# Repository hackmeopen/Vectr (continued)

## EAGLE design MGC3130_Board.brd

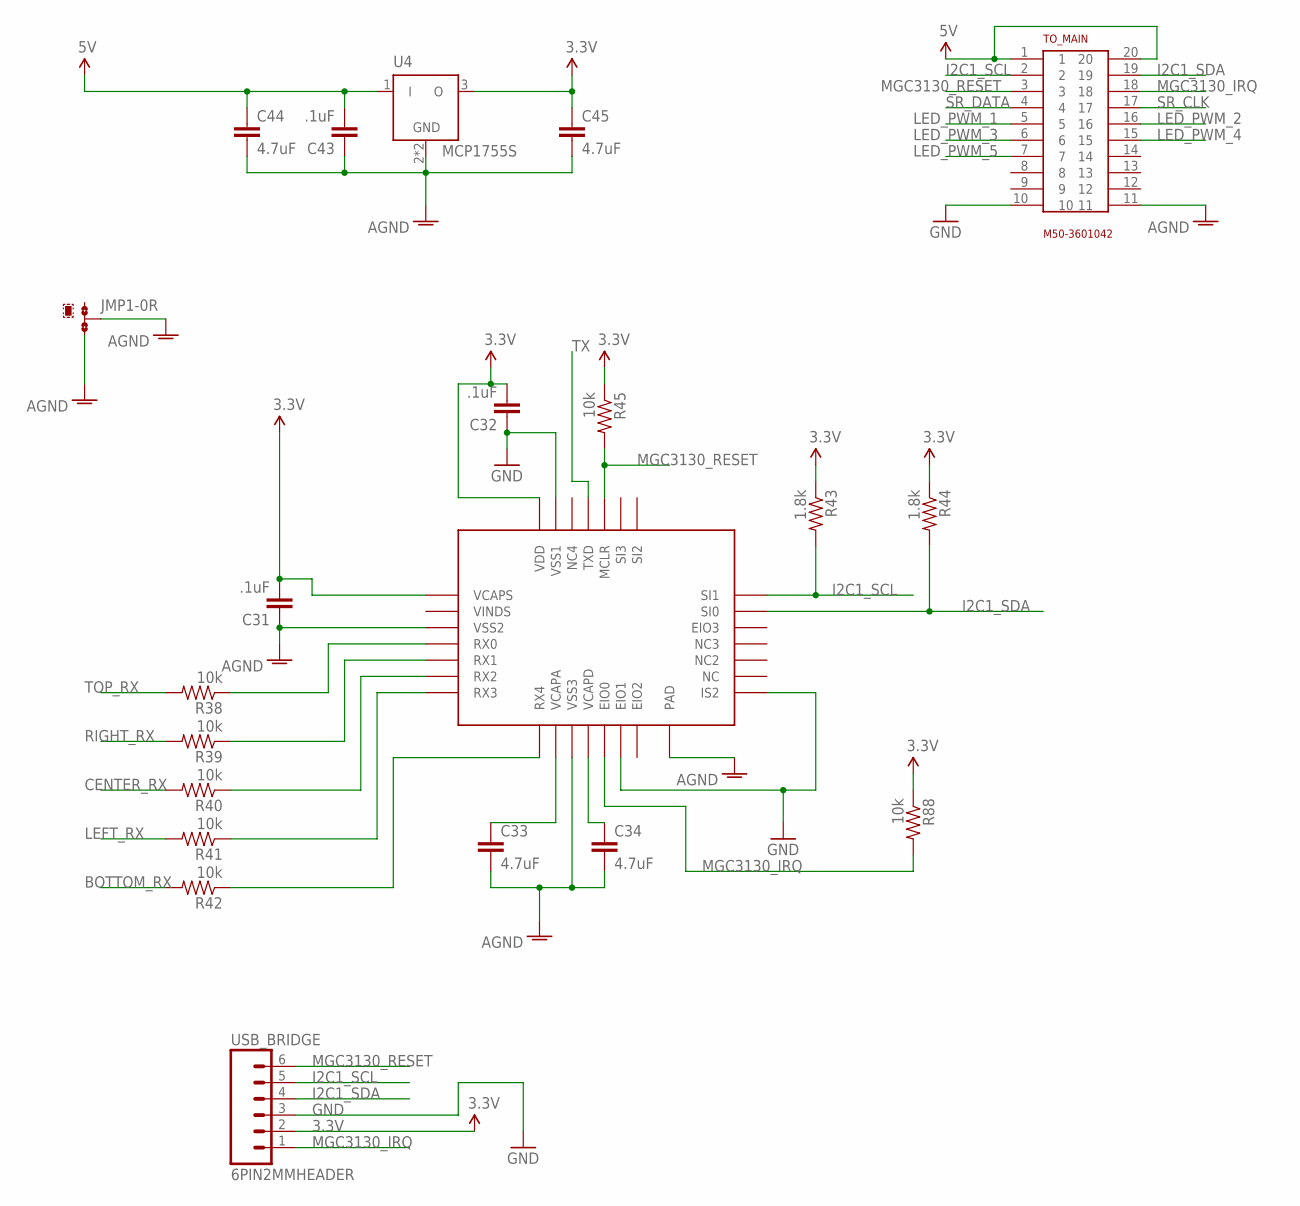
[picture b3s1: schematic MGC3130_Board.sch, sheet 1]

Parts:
C31, C32, C43: .1uF; 0603-CAP
C33, C34, C44, C45: 4.7uF; 1206
JMP1: 0R-JUMPA; A0R-JMP
R38, R39, R40, R41, R42, R45, R88: 10k; 0603-RES
R43, R44: 1.8k; 0603-RES
TO_MAIN: M50-3601042
U4: MCP1755S; SOT223
U14: MGC3130; QFN28
USB_BRIDGE: 6PIN2MMHEADER; 1X06_SMD_STRAIGHT

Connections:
3.3V: C31.2, C32.2, C45.1, R43.1, R44.1, R45.1, R88.1, U4.3 (O), U14.P$1 (VCAPS), U14.P$28 (VDD), USB_BRIDGE.2
5V: C43.2, C44.1, TO_MAIN.1, TO_MAIN.20, U4.1 (I); also elsewhere on the board
AGND: C31.1, C33.2, C34.2, C43.1, C44.2, C45.2, JMP1.2, JMP1.3, TO_MAIN.11, U4.2 (GND), U4.4 (GND), U14.P$3 (VSS2), U14.P$10 (VSS3), U14.P$29 (PAD)
BOTTOM_RX: R42.2
CENTER_RX: R40.2
GND: C32.1, TO_MAIN.10, U14.P$13 (EIO1), U14.P$15 (IS2), U14.P$27 (VSS1), USB_BRIDGE.3; also elsewhere on the board
I2C1_SCL: R43.2, TO_MAIN.2, U14.P$21 (SI1), USB_BRIDGE.5
I2C1_SDA: R44.2, TO_MAIN.19, U14.P$20 (SI0), USB_BRIDGE.4
LED_PWM_1: TO_MAIN.5; also elsewhere on the board
LED_PWM_2: TO_MAIN.16; also elsewhere on the board
LED_PWM_3: TO_MAIN.6; also elsewhere on the board
LED_PWM_4: TO_MAIN.15; also elsewhere on the board
LED_PWM_5: TO_MAIN.7; also elsewhere on the board
LEFT_RX: R41.2
MGC3130_IRQ: R88.2, TO_MAIN.18, U14.P$12 (EIO0), USB_BRIDGE.1
MGC3130_RESET: R45.2, TO_MAIN.3, U14.P$24 (MCLR), USB_BRIDGE.6
unnamed: R38.1, U14.P$4 (RX0)
unnamed: R39.1, U14.P$5 (RX1)
unnamed: R40.1, U14.P$6 (RX2)
unnamed: R41.1, U14.P$7 (RX3)
unnamed: R42.1, U14.P$8 (RX4)
unnamed: C33.1, U14.P$9 (VCAPA)
unnamed: C34.1, U14.P$11 (VCAPD)
RIGHT_RX: R39.2
SR_CLK: TO_MAIN.17; also elsewhere on the board
SR_DATA: TO_MAIN.4; also elsewhere on the board
TOP_RX: R38.2
TX: U14.P$25 (TXD)

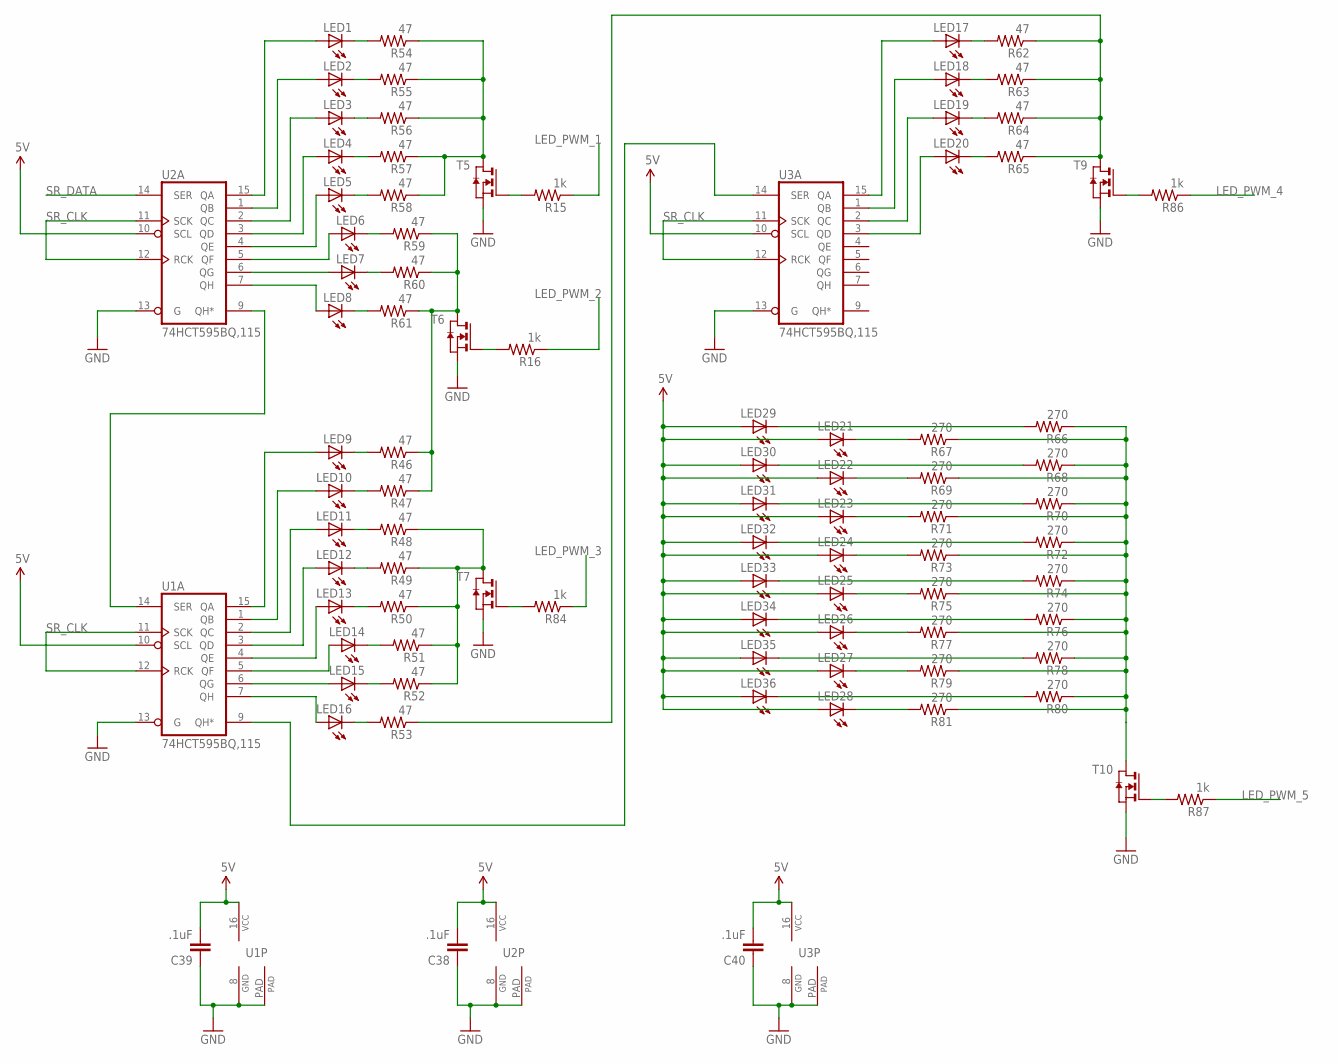
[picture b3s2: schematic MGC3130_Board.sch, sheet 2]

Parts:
C38, C39, C40: .1uF; 0603-CAP
LED1, LED2, LED3, LED4, LED5, LED6, LED7, LED8, LED9, LED10, LED11, LED12, LED13, LED14, LED15, LED16, LED17, LED18, LED19, LED20: APA3010QBC/D-GX; APA3010
LED21, LED22, LED23, LED24, LED25, LED26, LED27, LED28, LED29, LED30, LED31, LED32, LED33, LED34, LED35, LED36: APA3010SRCPRV-GX; APA3010
R15, R16, R84, R86, R87: 1k; 0603-RES
R46, R47, R48, R49, R50, R51, R52, R53, R54, R55, R56, R57, R58, R59, R60, R61, R62, R63, R64, R65: 47; 0603-RES
R66, R67, R68, R69, R70, R71, R72, R73, R74, R75, R76, R77, R78, R79, R80, R81: 270; 0603-RES
T5, T6, T7, T9, T10: NMOSSOT23; SOT-23
U1, U2, U3: 74HCT595BQ,115; DHVQFN16

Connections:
5V: C38.2, C39.2, C40.2, LED21.P$2 (A), LED22.P$2 (A), LED23.P$2 (A), LED24.P$2 (A), LED25.P$2 (A), LED26.P$2 (A), LED27.P$2 (A), LED28.P$2 (A), LED29.P$2 (A), LED30.P$2 (A), LED31.P$2 (A), LED32.P$2 (A), LED33.P$2 (A), LED34.P$2 (A), LED35.P$2 (A), LED36.P$2 (A), U1.10 (SCL), U1.16 (VCC), U2.10 (SCL), U2.16 (VCC), U3.10 (SCL), U3.16 (VCC); also elsewhere on the board
GND: C38.1, C39.1, C40.1, T5.2 (S), T6.2 (S), T7.2 (S), T9.2 (S), T10.2 (S), U1.8 (GND), U1.13 (G), U1.PAD (GND1), U2.8 (GND), U2.13 (G), U2.PAD (GND1), U3.8 (GND), U3.13 (G), U3.PAD (GND1); also elsewhere on the board
LED_PWM_1: R15.1; also elsewhere on the board
LED_PWM_2: R16.1; also elsewhere on the board
LED_PWM_3: R84.1; also elsewhere on the board
LED_PWM_4: R86.1; also elsewhere on the board
LED_PWM_5: R87.1; also elsewhere on the board
unnamed: LED29.P$1 (C), R66.2
unnamed: LED21.P$1 (C), R67.2
unnamed: LED30.P$1 (C), R68.2
unnamed: LED22.P$1 (C), R69.2
unnamed: LED31.P$1 (C), R70.2
unnamed: LED15.P$2 (A), U1.6 (QG)
unnamed: LED23.P$1 (C), R71.2
unnamed: LED32.P$1 (C), R72.2
unnamed: LED24.P$1 (C), R73.2
unnamed: LED34.P$1 (C), R76.2
unnamed: LED33.P$1 (C), R74.2
unnamed: LED25.P$1 (C), R75.2
unnamed: LED26.P$1 (C), R77.2
unnamed: LED35.P$1 (C), R78.2
unnamed: LED27.P$1 (C), R79.2
unnamed: R15.2, T5.3 (G)
unnamed: LED36.P$1 (C), R80.2
unnamed: LED28.P$1 (C), R81.2
unnamed: LED1.P$2 (A), U2.15 (QA)
unnamed: LED2.P$2 (A), U2.1 (QB)
unnamed: LED3.P$2 (A), U2.2 (QC)
unnamed: LED4.P$2 (A), U2.3 (QD)
unnamed: LED5.P$2 (A), U2.4 (QE)
unnamed: LED6.P$2 (A), U2.5 (QF)
unnamed: LED7.P$2 (A), U2.6 (QG)
unnamed: LED8.P$2 (A), U2.7 (QH)
unnamed: LED1.P$1 (C), R54.2
unnamed: LED2.P$1 (C), R55.2
unnamed: LED3.P$1 (C), R56.2
unnamed: LED4.P$1 (C), R57.2
unnamed: LED5.P$1 (C), R58.2
unnamed: LED6.P$1 (C), R59.2
unnamed: LED7.P$1 (C), R60.2
unnamed: LED8.P$1 (C), R61.2
unnamed: R54.1, R55.1, R56.1, R57.1, R58.1, T5.1 (D)
unnamed: R46.1, R47.1, R59.1, R60.1, R61.1, T6.1 (D)
unnamed: LED9.P$2 (A), U1.15 (QA)
unnamed: LED10.P$2 (A), U1.1 (QB)
unnamed: LED11.P$2 (A), U1.2 (QC)
unnamed: LED12.P$2 (A), U1.3 (QD)
unnamed: LED13.P$2 (A), U1.4 (QE)
unnamed: LED14.P$2 (A), U1.5 (QF)
unnamed: LED16.P$2 (A), U1.7 (QH)
unnamed: LED9.P$1 (C), R46.2
unnamed: LED10.P$1 (C), R47.2
unnamed: LED11.P$1 (C), R48.2
unnamed: LED12.P$1 (C), R49.2
unnamed: LED13.P$1 (C), R50.2
unnamed: LED14.P$1 (C), R51.2
unnamed: LED15.P$1 (C), R52.2
unnamed: LED16.P$1 (C), R53.2
unnamed: R48.1, R49.1, R50.1, R51.1, R52.1, T7.1 (D)
unnamed: LED17.P$2 (A), U3.15 (QA)
unnamed: LED18.P$2 (A), U3.1 (QB)
unnamed: LED19.P$2 (A), U3.2 (QC)
unnamed: LED20.P$2 (A), U3.3 (QD)
unnamed: R66.1, R67.1, R68.1, R69.1, R70.1, R71.1, R72.1, R73.1, R74.1, R75.1, R76.1, R77.1, R78.1, R79.1, R80.1, R81.1, T10.1 (D)
unnamed: U1.14 (SER), U2.9 (QH*)
unnamed: LED17.P$1 (C), R62.2
unnamed: LED18.P$1 (C), R63.2
unnamed: LED19.P$1 (C), R64.2
unnamed: LED20.P$1 (C), R65.2
unnamed: R53.1, R62.1, R63.1, R64.1, R65.1, T9.1 (D)
unnamed: U1.9 (QH*), U3.14 (SER)
unnamed: R16.2, T6.3 (G)
unnamed: R84.2, T7.3 (G)
unnamed: R86.2, T9.3 (G)
unnamed: R87.2, T10.3 (G)
SR_CLK: U1.11 (SCK), U1.12 (RCK), U2.11 (SCK), U2.12 (RCK), U3.11 (SCK), U3.12 (RCK); also elsewhere on the board
SR_DATA: U2.14 (SER); also elsewhere on the board

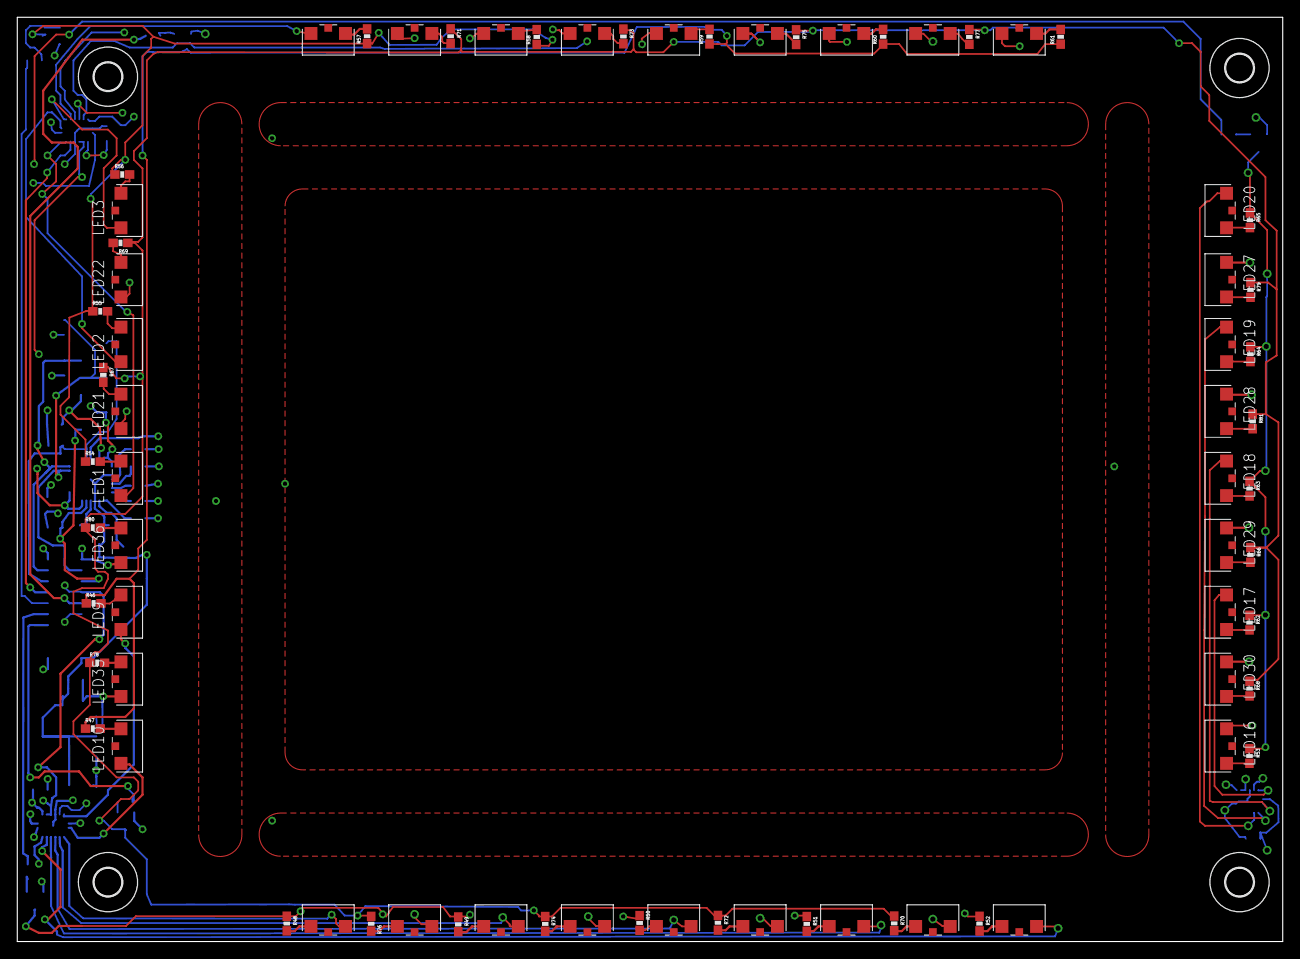
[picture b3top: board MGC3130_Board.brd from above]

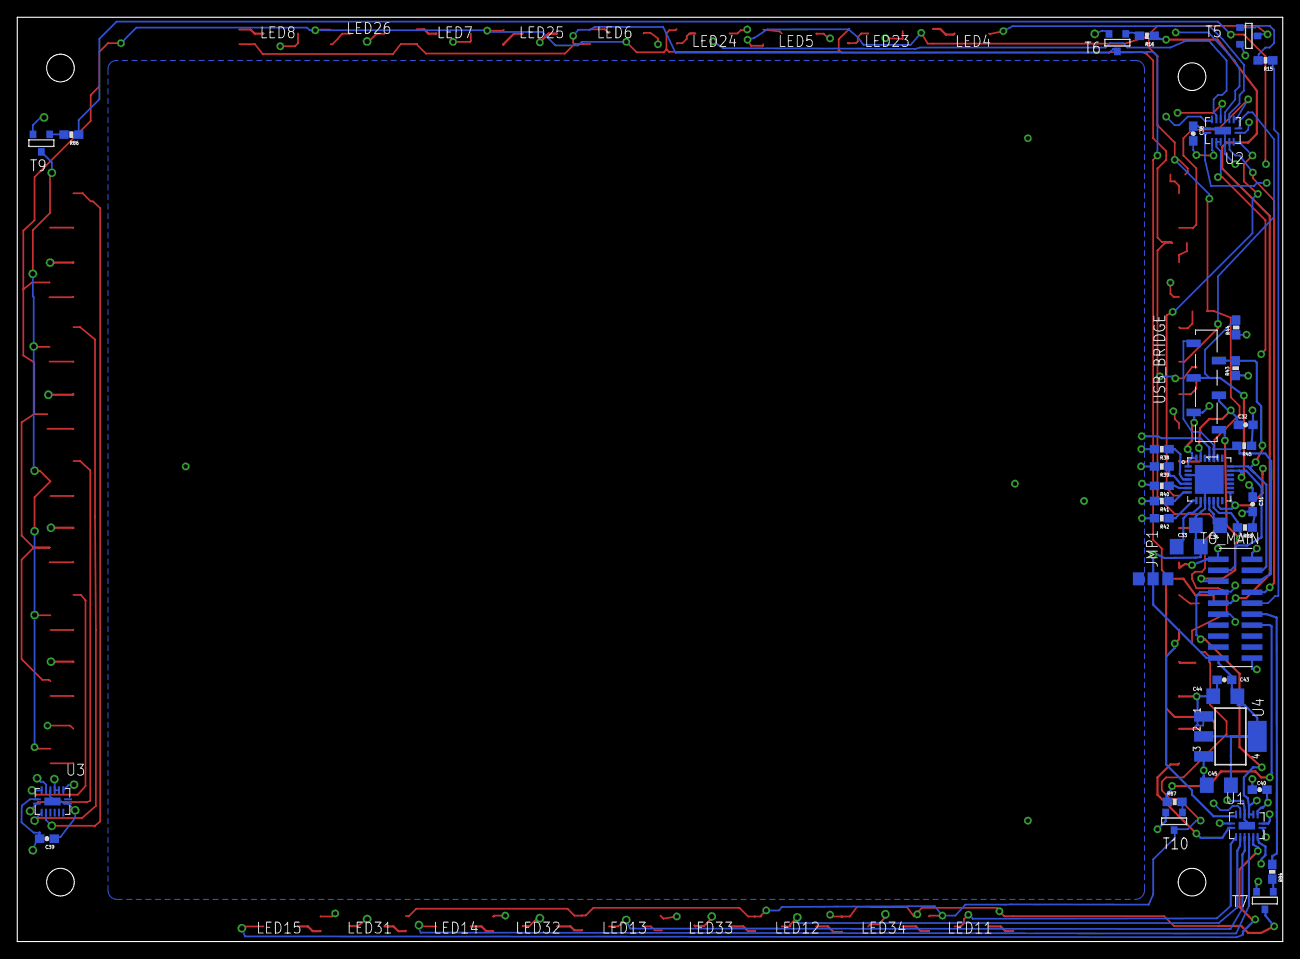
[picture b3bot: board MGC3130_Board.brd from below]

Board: 4 copper layers, 146.5 x 107.0 mm, 113 parts (36 on the bottom side), 90 nets.

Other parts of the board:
U$1, U$2, U$3, U$4: 3,2

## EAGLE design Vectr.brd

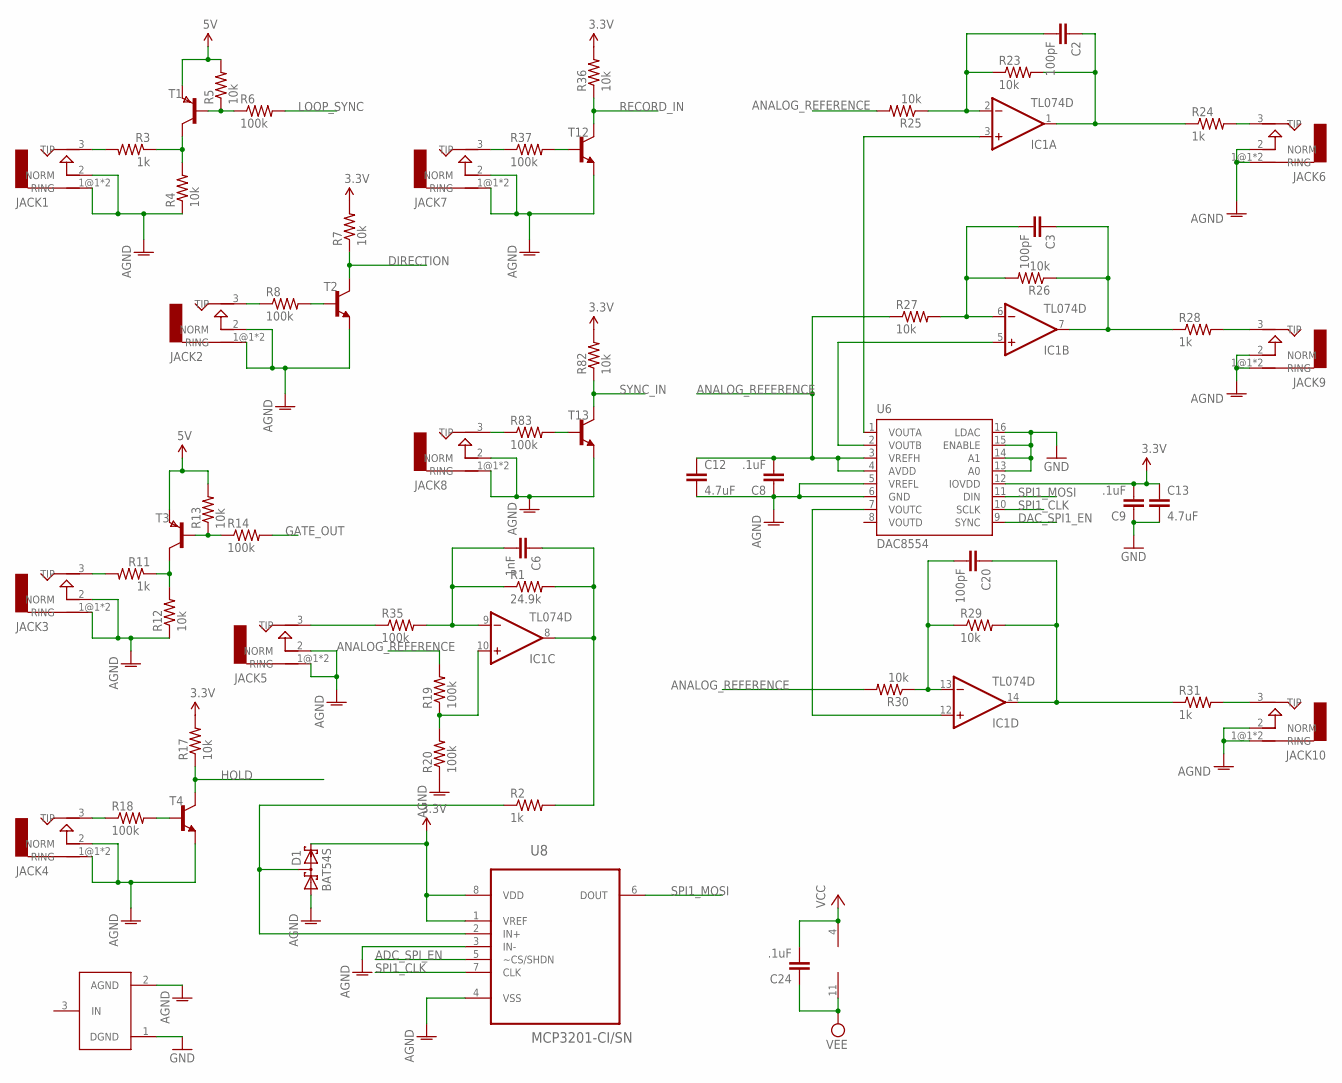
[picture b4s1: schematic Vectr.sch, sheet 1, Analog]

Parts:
C2, C3, C20: 100pF; 0603-CAP
C6: 1nF; 0603-CAP
C8, C9, C24: .1uF; 0603-CAP
C12, C13: 4.7uF; 1206
D1: BAT54S; SOT23
IC1: TL074D; SO14
JACK1, JACK2, JACK3, JACK4, JACK5, JACK6, JACK7, JACK8, JACK9, JACK10: AUDIO-JACKERTHENVAR; ERTHENVAR-JACK
R1: 24.9k; 0603-RES
R2, R3, R11, R24, R28, R31: 1k; 0603-RES
R4, R5, R7, R12, R13, R17, R23, R25, R26, R27, R29, R30, R36, R82: 10k; 0603-RES
R6, R8, R14, R18, R19, R20, R35, R37, R83: 100k; 0603-RES
T1, T3: PNPSOT23; SOT-23
T2, T4, T12, T13: -NPN-SOT23-EBC; SOT23-EBC
U6: DAC8554; PW_R-PDSO-G16
U8: MCP3201-CI/SN; SOIC127P600X175-8N
U$11: GND_CONNECT

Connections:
3.3V: C9.2, C13.1, D1.2 (C2), R7.2, R17.2, R36.2, R82.2, U6.12 (IOVDD), U8.1 (VREF), U8.8 (VDD); also elsewhere on the board
5V: R5.2, R13.2, T1.2 (E), T3.2 (E); also elsewhere on the board
ADC_SPI_EN: U8.5 (~CS/SHDN); also elsewhere on the board
AGND: C8.1, C12.2, D1.1 (A1), JACK1.1@1 (RING), JACK1.1@2 (RING), JACK1.2 (NORM), JACK2.1@1 (RING), JACK2.1@2 (RING), JACK2.2 (NORM), JACK3.1@1 (RING), JACK3.1@2 (RING), JACK3.2 (NORM), JACK4.1@1 (RING), JACK4.1@2 (RING), JACK4.2 (NORM), JACK5.1@1 (RING), JACK5.1@2 (RING), JACK5.2 (NORM), JACK6.1@1 (RING), JACK6.1@2 (RING), JACK6.2 (NORM), JACK7.1@1 (RING), JACK7.1@2 (RING), JACK7.2 (NORM), JACK8.1@1 (RING), JACK8.1@2 (RING), JACK8.2 (NORM), JACK9.1@1 (RING), JACK9.1@2 (RING), JACK9.2 (NORM), JACK10.1@1 (RING), JACK10.1@2 (RING), JACK10.2 (NORM), R4.1, R12.1, R20.1, T2.E, T4.E, T12.E, T13.E, U6.5 (VREFL), U6.6 (GND), U8.3 (IN-), U8.4 (VSS), U$11.2 (AGND); also elsewhere on the board
ANALOG_REFERENCE: C8.2, C12.1, R19.2, R25.2, R27.1, R30.2, U6.3 (VREFH), U6.4 (AVDD); also elsewhere on the board
DAC_SPI1_EN: U6.9 (SYNC); also elsewhere on the board
DIRECTION: R7.1, T2.C; also elsewhere on the board
GATE_OUT: R14.2; also elsewhere on the board
GND: C9.1, C13.2, U6.13 (A0), U6.14 (A1), U6.15 (ENABLE), U6.16 (LDAC), U$11.1 (DGND); also elsewhere on the board
HOLD: R17.1, T4.C; also elsewhere on the board
LOOP_SYNC: R6.2; also elsewhere on the board
unnamed: R5.1, R6.1, T1.3 (B)
unnamed: C2.2, IC1.2 (-IN), R23.1, R25.1
unnamed: C2.1, IC1.1 (OUT), R23.2, R24.1
unnamed: R3.1, R4.2, T1.1 (C)
unnamed: JACK1.3 (TIP), R3.2
unnamed: IC1.5 (+IN), U6.2 (VOUTB)
unnamed: JACK2.3 (TIP), R8.1
unnamed: R8.2, T2.B
unnamed: C3.2, IC1.6 (-IN), R26.2, R27.2
unnamed: R13.1, R14.1, T3.3 (B)
unnamed: R11.1, R12.2, T3.1 (C)
unnamed: JACK3.3 (TIP), R11.2
unnamed: C3.1, IC1.7 (OUT), R26.1, R28.1
unnamed: R18.2, T4.B
unnamed: JACK4.3 (TIP), R18.1
unnamed: C20.2, IC1.13 (-IN), R29.1, R30.1
unnamed: C20.1, IC1.14 (OUT), R29.2, R31.1
unnamed: C6.2, IC1.9 (-IN), R1.1, R35.2
unnamed: IC1.3 (+IN), U6.1 (VOUTA)
unnamed: D1.3 (C1A2), R2.1, U8.2 (IN+)
unnamed: JACK6.3 (TIP), R24.2
unnamed: JACK5.3 (TIP), R35.1
unnamed: C6.1, IC1.8 (OUT), R1.2, R2.2
unnamed: IC1.10 (+IN), R19.1, R20.2
unnamed: JACK7.3 (TIP), R37.1
unnamed: JACK9.3 (TIP), R28.2
unnamed: R37.2, T12.B
unnamed: IC1.12 (+IN), U6.7 (VOUTC)
unnamed: JACK10.3 (TIP), R31.2
unnamed: JACK8.3 (TIP), R83.1
unnamed: R83.2, T13.B
RECORD_IN: R36.1, T12.C; also elsewhere on the board
SPI1_CLK: U6.10 (SCLK), U8.7 (CLK); also elsewhere on the board
SPI1_MOSI: U6.11 (DIN), U8.6 (DOUT); also elsewhere on the board
SYNC_IN: R82.1, T13.C; also elsewhere on the board
VCC: C24.2, IC1.4 (V+); also elsewhere on the board
VEE: C24.1, IC1.11 (V-); also elsewhere on the board

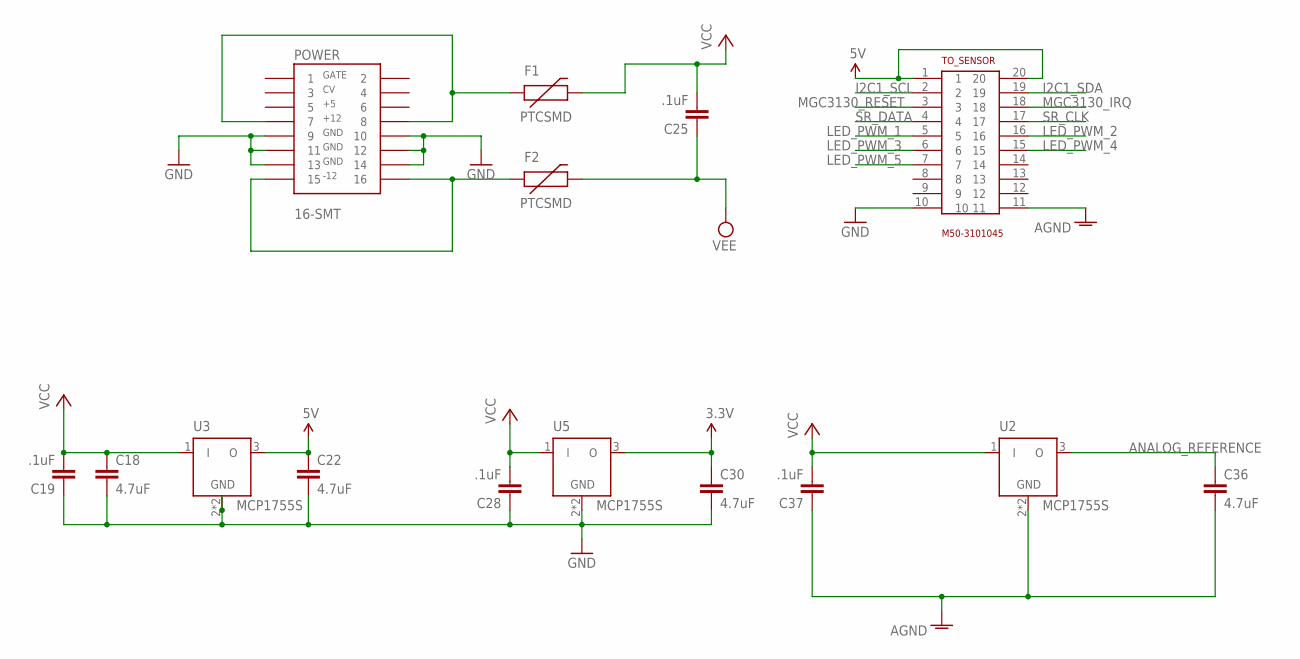
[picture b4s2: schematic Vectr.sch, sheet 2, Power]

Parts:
C18, C22, C30, C36: 4.7uF; 1206
C19, C25, C28, C37: .1uF; 0603-CAP
F1, F2: PTCSMD; PTC-1206
POWER: 16-SMT
TO_SENSOR: M50-3101045
U2, U3, U5: MCP1755S; SOT223

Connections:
3.3V: C30.1, U5.3 (O); also elsewhere on the board
5V: C22.1, TO_SENSOR.1, TO_SENSOR.20, U3.3 (O); also elsewhere on the board
AGND: C36.2, C37.1, TO_SENSOR.11, U2.2 (GND), U2.4 (GND); also elsewhere on the board
ANALOG_REFERENCE: C36.1, U2.3 (O); also elsewhere on the board
GND: C18.2, C19.1, C22.2, C28.1, C30.2, POWER.P$9 (9), POWER.P$10 (10), POWER.P$11 (11), POWER.P$12 (12), POWER.P$13 (13), POWER.P$14 (14), TO_SENSOR.10, U3.2 (GND), U3.4 (GND), U5.2 (GND), U5.4 (GND); also elsewhere on the board
I2C1_SCL: TO_SENSOR.2; also elsewhere on the board
I2C1_SDA: TO_SENSOR.19; also elsewhere on the board
LED_PWM_1: TO_SENSOR.5; also elsewhere on the board
LED_PWM_2: TO_SENSOR.16; also elsewhere on the board
LED_PWM_3: TO_SENSOR.6; also elsewhere on the board
LED_PWM_4: TO_SENSOR.15; also elsewhere on the board
LED_PWM_5: TO_SENSOR.7; also elsewhere on the board
MGC3130_IRQ: TO_SENSOR.18; also elsewhere on the board
MGC3130_RESET: TO_SENSOR.3; also elsewhere on the board
unnamed: F1.1, POWER.P$7 (7), POWER.P$8 (8)
unnamed: F2.1, POWER.P$15 (15), POWER.P$16 (16)
SR_CLK: TO_SENSOR.17; also elsewhere on the board
SR_DATA: TO_SENSOR.4; also elsewhere on the board
VCC: C18.1, C19.2, C25.2, C28.2, C37.2, F1.2, U2.1 (I), U3.1 (I), U5.1 (I); also elsewhere on the board
VEE: C25.1, F2.2; also elsewhere on the board

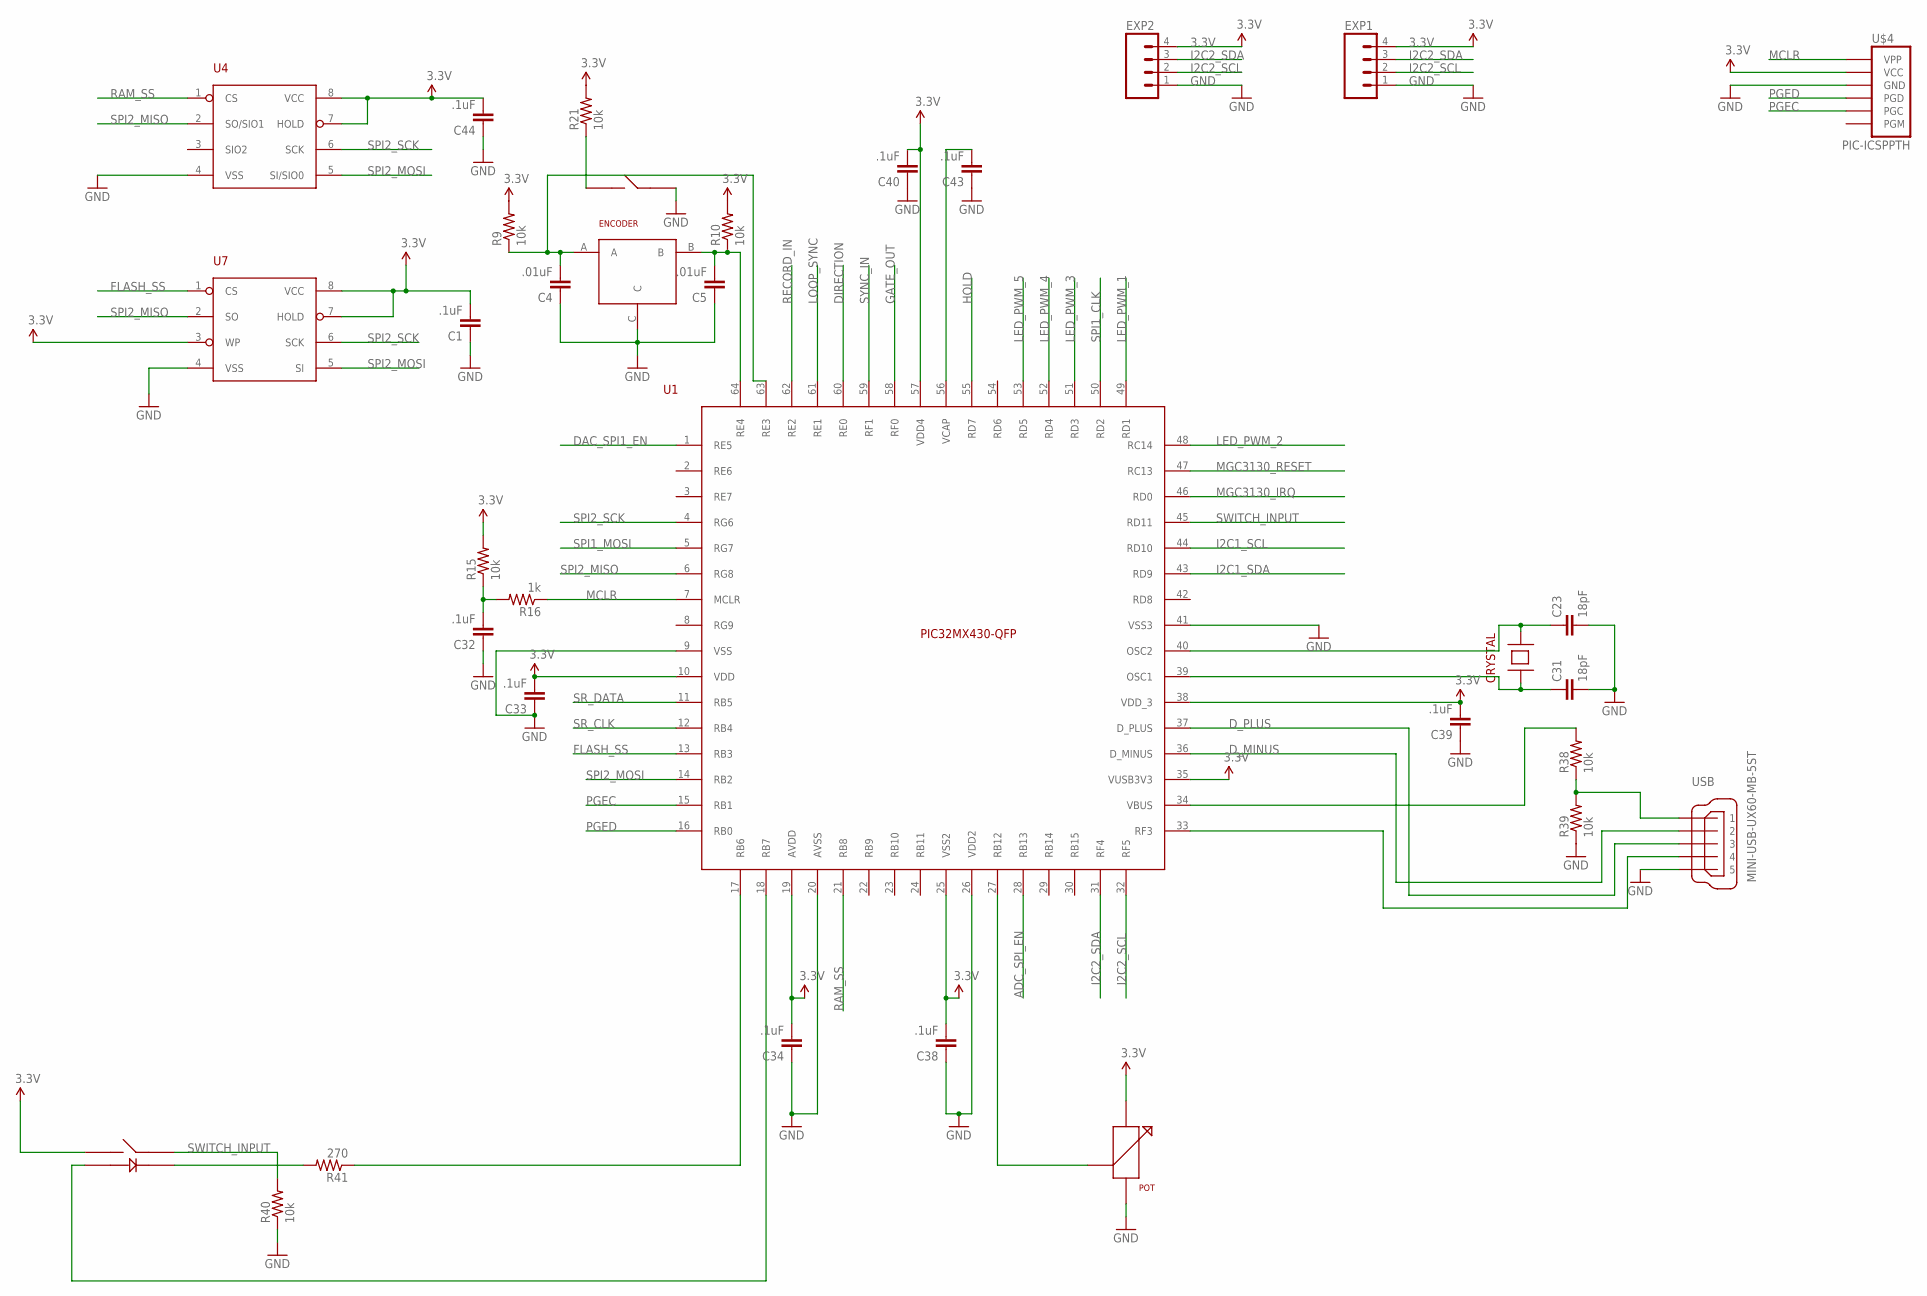
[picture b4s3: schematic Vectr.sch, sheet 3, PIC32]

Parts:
C1, C32, C33, C34, C38, C39, C40, C43, C44: .1uF; 0603-CAP
C4, C5: .01uF; 0603-CAP
C23, C31: 18pF; 0603-CAP
CRYSTAL: SMD-4-CRYSTAL
ENCODER: PEC16_ENCODER
EXP1, EXP2: M04SMD_STRAIGHT_COMBO; 1X04_SMD_STRAIGHT_COMBO
POT: 9MMPOT
R9, R10, R15, R21, R38, R39, R40: 10k; 0603-RES
R16: 1k; 0603-RES
R41: 270; 0603-RES
U1: PIC32MX430-QFP; QFP50P1200X1200X120-64N
U4: 23LC512; SO-08
U7: SST25VF010A; SO-08
U$2: 5GSH9
U$4: PIC-ICSPPTH; MOLEX-1X6
USB: MINI-USB-UX60-MB-5ST; UX60-MB-5ST

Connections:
3.3V: C1.2, C33.2, C34.2, C38.2, C39.2, C40.2, C44.2, EXP1.4, EXP2.4, POT.1, R9.2, R10.2, R15.2, R21.2, U1.10 (VDD), U1.19 (AVDD), U1.25 (VSS2), U1.35 (VUSB3V3), U1.38 (VDD_3), U1.57 (VDD4), U4.7 (HOLD), U4.8 (VCC), U7.3 (WP), U7.7 (HOLD), U7.8 (VCC), U$2.1, U$4.5 (VCC); also elsewhere on the board
ADC_SPI_EN: U1.28 (RB13); also elsewhere on the board
DAC_SPI1_EN: U1.1 (RE5); also elsewhere on the board
DIRECTION: U1.60 (RE0); also elsewhere on the board
D_MINUS: U1.36 (D_MINUS), USB.2
D_PLUS: U1.37 (D_PLUS), USB.3
FLASH_SS: U1.13 (RB3), U7.1 (CS)
GATE_OUT: U1.58 (RF0); also elsewhere on the board
GND: C1.1, C4.1, C5.1, C23.2, C31.2, C32.1, C33.1, C34.1, C38.1, C39.1, C40.1, C43.1, C44.1, ENCODER.C, ENCODER.E, EXP1.1, EXP2.1, POT.3, R39.1, R40.1, U1.9 (VSS), U1.20 (AVSS), U1.26 (VDD2), U1.41 (VSS3), U4.4 (VSS), U7.4 (VSS), U$4.4 (GND), USB.5; also elsewhere on the board
HOLD: U1.55 (RD7); also elsewhere on the board
I2C1_SCL: U1.44 (RD10); also elsewhere on the board
I2C1_SDA: U1.43 (RD9); also elsewhere on the board
I2C2_SCL: EXP1.2, EXP2.2, U1.32 (RF5)
I2C2_SDA: EXP1.3, EXP2.3, U1.31 (RF4)
LED_PWM_1: U1.49 (RD1); also elsewhere on the board
LED_PWM_2: U1.48 (RC14); also elsewhere on the board
LED_PWM_3: U1.51 (RD3); also elsewhere on the board
LED_PWM_4: U1.52 (RD4); also elsewhere on the board
LED_PWM_5: U1.53 (RD5); also elsewhere on the board
LOOP_SYNC: U1.61 (RE1); also elsewhere on the board
MCLR: R16.1, U1.7 (MCLR), U$4.6 (VPP)
MGC3130_IRQ: U1.46 (RD0); also elsewhere on the board
MGC3130_RESET: U1.47 (RC13); also elsewhere on the board
unnamed: C32.2, R15.1, R16.2
unnamed: C5.2, ENCODER.B, R10.1, U1.64 (RE4)
unnamed: C4.2, ENCODER.A, R9.1, U1.63 (RE3)
unnamed: POT.2, U1.27 (RB12)
unnamed: U1.18 (RB7), U$2.3
unnamed: ENCODER.D, R21.1
unnamed: C23.1, CRYSTAL.3, U1.40 (OSC2)
unnamed: C31.1, CRYSTAL.1, U1.39 (OSC1)
unnamed: R38.1, R39.2, USB.1
unnamed: C43.2, U1.56 (VCAP)
unnamed: R38.2, U1.34 (VBUS)
unnamed: U1.33 (RF3), USB.4
unnamed: R41.2, U$2.2
PGEC: U1.15 (RB1), U$4.2 (PGC)
PGED: U1.16 (RB0), U$4.3 (PGD)
RAM_SS: U1.21 (RB8), U4.1 (CS)
RECORD_IN: U1.62 (RE2); also elsewhere on the board
SPI1_CLK: U1.50 (RD2); also elsewhere on the board
SPI1_MOSI: U1.5 (RG7); also elsewhere on the board
SPI2_MISO: U1.6 (RG8), U4.2 (SO/SIO1), U7.2 (SO)
SPI2_MOSI: U1.14 (RB2), U4.5 (SI/SIO0), U7.5 (SI)
SPI2_SCK: U1.4 (RG6), U4.6 (SCK), U7.6 (SCK)
SR_CLK: U1.12 (RB4); also elsewhere on the board
SR_DATA: U1.11 (RB5); also elsewhere on the board
SWITCH_INPUT: R40.2, U1.45 (RD11), U$2.4
SWITCH_LED1: R41.1, U1.17 (RB6)
SYNC_IN: U1.59 (RF1); also elsewhere on the board

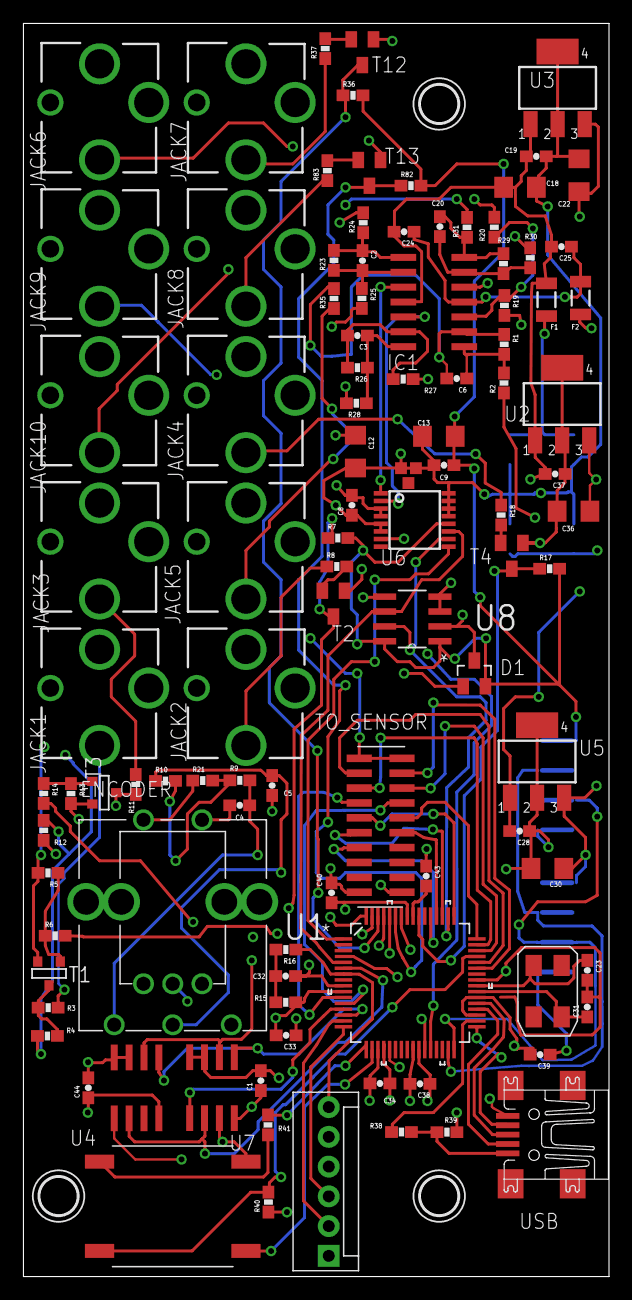
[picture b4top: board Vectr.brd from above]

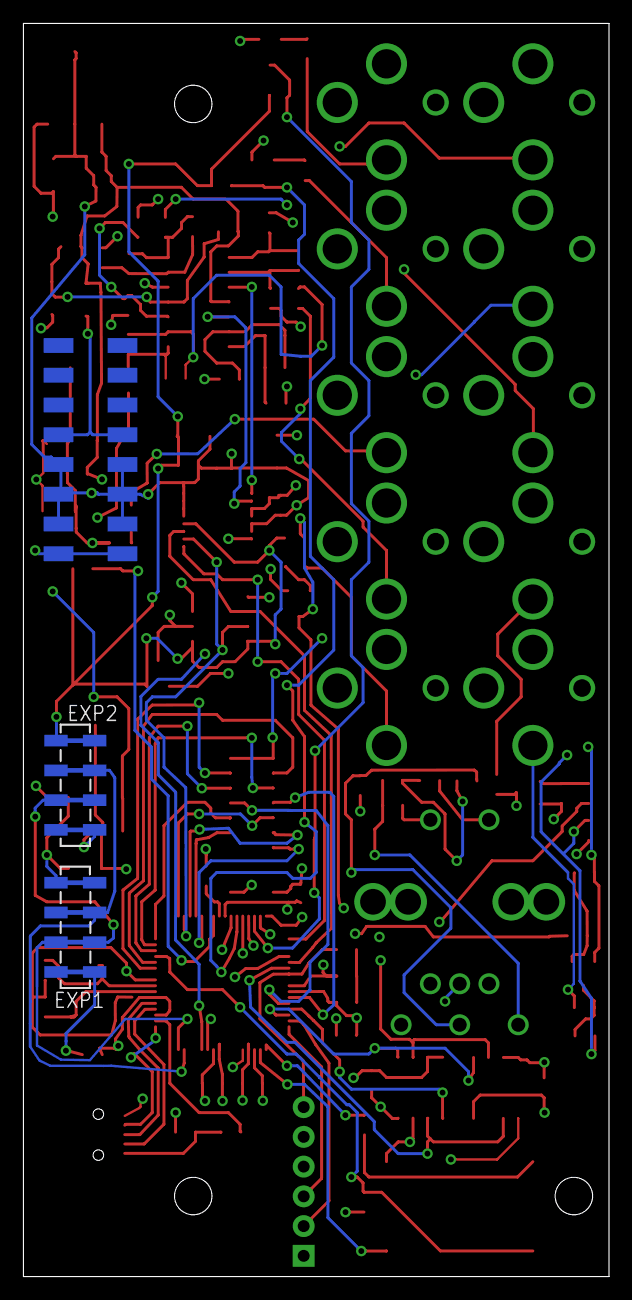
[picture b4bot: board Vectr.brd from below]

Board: 4 copper layers, 50.0 x 107.0 mm, 111 parts (3 on the bottom side), 88 nets.

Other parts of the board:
U$1, U$3, U$5: 3,2

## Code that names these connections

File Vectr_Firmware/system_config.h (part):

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#define I2C_MGC3130_SLAVE_ADDRESS   0x1A

/*MGC3130 Port Definitions*/
#define MGC3130_RESET_PORT          PORT_CHANNEL_C
#define MGC3130_RESET_PIN           PORTS_BIT_POS_13
#define MGC3130_ACTIVATE_RESET      PLIB_PORTS_PinClear(PORTS_ID_0, MGC3130_RESET_PORT,MGC3130_RESET_PIN)
#define MGC3130_CLEAR_RESET         PLIB_PORTS_PinSet(PORTS_ID_0, MGC3130_RESET_PORT,MGC3130_RESET_PIN)

#define MGC3130_TS_PORT     PORT_CHANNEL_D
#define MGC3130_TS_PIN      PORTS_BIT_POS_0
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#define DAC_LDAC_PORT   PORT_CHANNEL_E
#define DAC_LDAC_PIN    PORTS_BIT_POS_6

#define ADC_SPI_EN_PORT PORT_CHANNEL_B
#define ADC_SPI_EN_PIN  PORTS_BIT_POS_13

#define SPI1_SCK_PORT   PORT_CHANNEL_D
#define SPI1_SCK_PIN    PORTS_BIT_POS_2

#define SPI1_MOSI_PORT  PORT_CHANNEL_G
#define SPI1_MOSI_PIN   PORTS_BIT_POS_7

#define SPI1_MISO_PORT  PORT_CHANNEL_E
#define SPI1_MISO_PIN   PORTS_BIT_POS_5

#define CLEAR_SPI1_TX_INT   PLIB_INT_SourceFlagClear(INT_ID_0, INT_SOURCE_SPI_1_TRANSMIT);
#define ENABLE_SPI1_TX_INT  PLIB_INT_SourceEnable(INT_ID_0, INT_SOURCE_SPI_1_TRANSMIT);
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/*SPI Macros*/
#define SET_DAC_SPI_EN  PLIB_PORTS_PinSet(PORTS_ID_0, DAC_SPI_EN_PORT,DAC_SPI_EN_PIN)
#define CLEAR_DAC_SPI_EN PLIB_PORTS_PinClear(PORTS_ID_0, DAC_SPI_EN_PORT,DAC_SPI_EN_PIN)
#define SET_ADC_SPI_EN PLIB_PORTS_PinSet(PORTS_ID_0, ADC_SPI_EN_PORT,ADC_SPI_EN_PIN)
#define CLEAR_ADC_SPI_EN PLIB_PORTS_PinClear(PORTS_ID_0, ADC_SPI_EN_PORT,ADC_SPI_EN_PIN)
#define SET_DAC_LDAC    PLIB_PORTS_PinSet(PORTS_ID_0, DAC_LDAC_PORT,DAC_LDAC_PIN)
#define CLEAR_DAC_LDAC  PLIB_PORTS_PinClear(PORTS_ID_0, DAC_LDAC_PORT,DAC_LDAC_PIN)

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#define SPI_MEM             SPI_ID_2
#define SPI_MEM_BAUD_RATE   10000000 

#define SPI2_SCK_PORT   PORT_CHANNEL_G
#define SPI2_SCK_PIN    PORTS_BIT_POS_6

#define SPI2_MOSI_PORT  PORT_CHANNEL_G
#define SPI2_MOSI_PIN   PORTS_BIT_POS_8

#define SPI2_MISO_PORT  PORT_CHANNEL_B
#define SPI2_MISO_PIN   PORTS_BIT_POS_3

#define RAM_SPI_EN_PORT PORT_CHANNEL_B
#define RAM_SPI_EN_PIN  PORTS_BIT_POS_8
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

/*GPIO Functionality*/
#define RECORD_IN_PORT  PORT_CHANNEL_E
#define RECORD_IN_PIN   PORTS_BIT_POS_2
#define LOOP_SYNC_PORT  PORT_CHANNEL_F
#define LOOP_SYNC_PIN   PORTS_BIT_POS_0
#define SYNC_IN_PORT  PORT_CHANNEL_E//Becomes sync
#define SYNC_IN_PIN   PORTS_BIT_POS_0
#define PLAY_IN_PORT    PORT_CHANNEL_F//Becomes play input
#define PLAY_IN_PIN     PORTS_BIT_POS_1
#define GATE_OUT_PORT   PORT_CHANNEL_E
#define GATE_OUT_PIN    PORTS_BIT_POS_1
#define HOLD_PORT       PORT_CHANNEL_D
#define HOLD_PIN        PORTS_BIT_POS_7
#define ENABLE_PORT_F_CHANGE_INTERRUPT    PLIB_INT_SourceEnable(INT_ID_0, INT_SOURCE_CHANGE_NOTICE_F)
#define DISABLE_PORT_F_CHANGE_INTERRUPT   PLIB_INT_SourceDisable(INT_ID_0, INT_SOURCE_CHANGE_NOTICE_F)
#define CLEAR_PORT_F_CHANGE_INTERRUPT     PLIB_INT_SourceFlagClear(INT_ID_0, INT_SOURCE_CHANGE_NOTICE_F)
#define ENABLE_PORT_D_CHANGE_INTERRUPT    PLIB_INT_SourceEnable(INT_ID_0, INT_SOURCE_CHANGE_NOTICE_D)
#define DISABLE_PORT_D_CHANGE_INTERRUPT   PLIB_INT_SourceDisable(INT_ID_0, INT_SOURCE_CHANGE_NOTICE_D)
#define CLEAR_PORT_D_CHANGE_INTERRUPT     PLIB_INT_SourceFlagClear(INT_ID_0, INT_SOURCE_CHANGE_NOTICE_D)
#define SET_GATE_OUT_PORT PLIB_PORTS_PinClear(PORTS_ID_0, GATE_OUT_PORT, GATE_OUT_PIN)
#define CLEAR_GATE_OUT_PORT PLIB_PORTS_PinSet(PORTS_ID_0, GATE_OUT_PORT, GATE_OUT_PIN)
#define SET_LOOP_SYNC_OUT   PLIB_PORTS_PinClear(PORTS_ID_0, LOOP_SYNC_PORT, LOOP_SYNC_PIN)
#define CLEAR_LOOP_SYNC_OUT PLIB_PORTS_PinSet(PORTS_ID_0, LOOP_SYNC_PORT, LOOP_SYNC_PIN)
#define PLAY_IN_IS_HIGH !PLIB_PORTS_PinGet(PORTS_ID_0, PLAY_IN_PORT, PLAY_IN_PIN)
#define REC_IN_IS_HIGH  !PLIB_PORTS_PinGet(PORTS_ID_0, RECORD_IN_PORT, RECORD_IN_PIN)

#define JACK_DETECT_PORT    PORT_CHANNEL_D
#define JACK_DETECT_PIN     PORTS_BIT_POS_8
#define READ_JACK_DETECT_PIN    PLIB_PORTS_PinGet(PORTS_ID_0, JACK_DETECT_PORT, JACK_DETECT_PIN)
#define MODULATION_JACK_PLUGGED_IN  !READ_JACK_DETECT_PIN


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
